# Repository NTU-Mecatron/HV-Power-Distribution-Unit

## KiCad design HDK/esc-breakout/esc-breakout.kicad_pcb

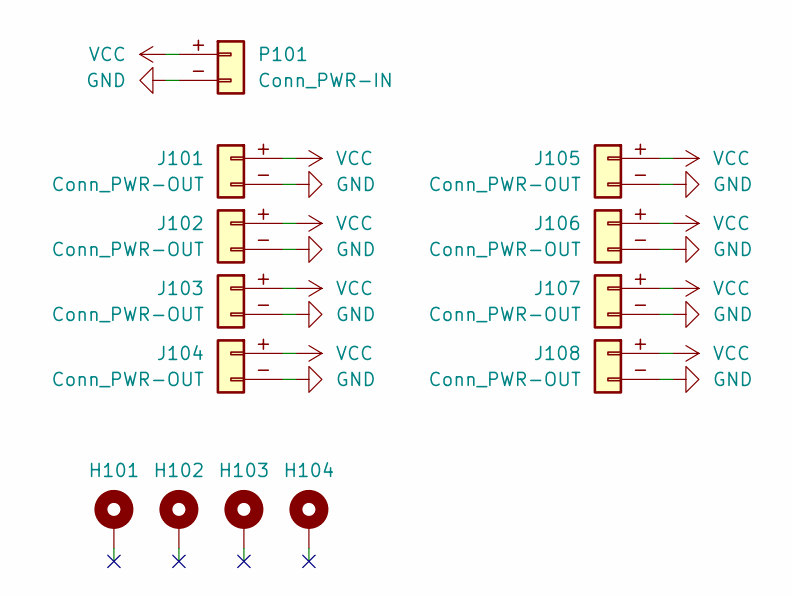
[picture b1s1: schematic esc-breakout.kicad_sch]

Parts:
H101, H102, H103, H104: MountingHole_Pad; MountingHole_3.2mm_M3_DIN965_Pad_TopBottom
J101, J102, J103, J104, J105, J106, J107, J108: Conn_PWR-OUT; AMASS_XT30UPB-F_1x02_P5.0mm_Vertical
P101: Conn_PWR-IN; AMASS_XT60-M_1x02_P7.20mm_Vertical

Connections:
GND: J101.- (Pin_2), J102.- (Pin_2), J103.- (Pin_2), J104.- (Pin_2), J105.- (Pin_2), J106.- (Pin_2), J107.- (Pin_2), J108.- (Pin_2), P101.- (Pin_2)
VCC: J101.+ (Pin_1), J102.+ (Pin_1), J103.+ (Pin_1), J104.+ (Pin_1), J105.+ (Pin_1), J106.+ (Pin_1), J107.+ (Pin_1), J108.+ (Pin_1), P101.+ (Pin_1)

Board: 2 copper layers, 13 parts (1 on the bottom side), 2 nets, no tracks yet.

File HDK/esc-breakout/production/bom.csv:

Designator,Footprint,Quantity,Value,LCSC Part #
"J101, J102, J103, J104, J105, J106, J107, J108",AMASS_XT30UPB-F_1x02_P5.0mm_Vertical,8,Conn_PWR-OUT,
P101,AMASS_XT60-M_1x02_P7.20mm_Vertical,1,Conn_PWR-IN,

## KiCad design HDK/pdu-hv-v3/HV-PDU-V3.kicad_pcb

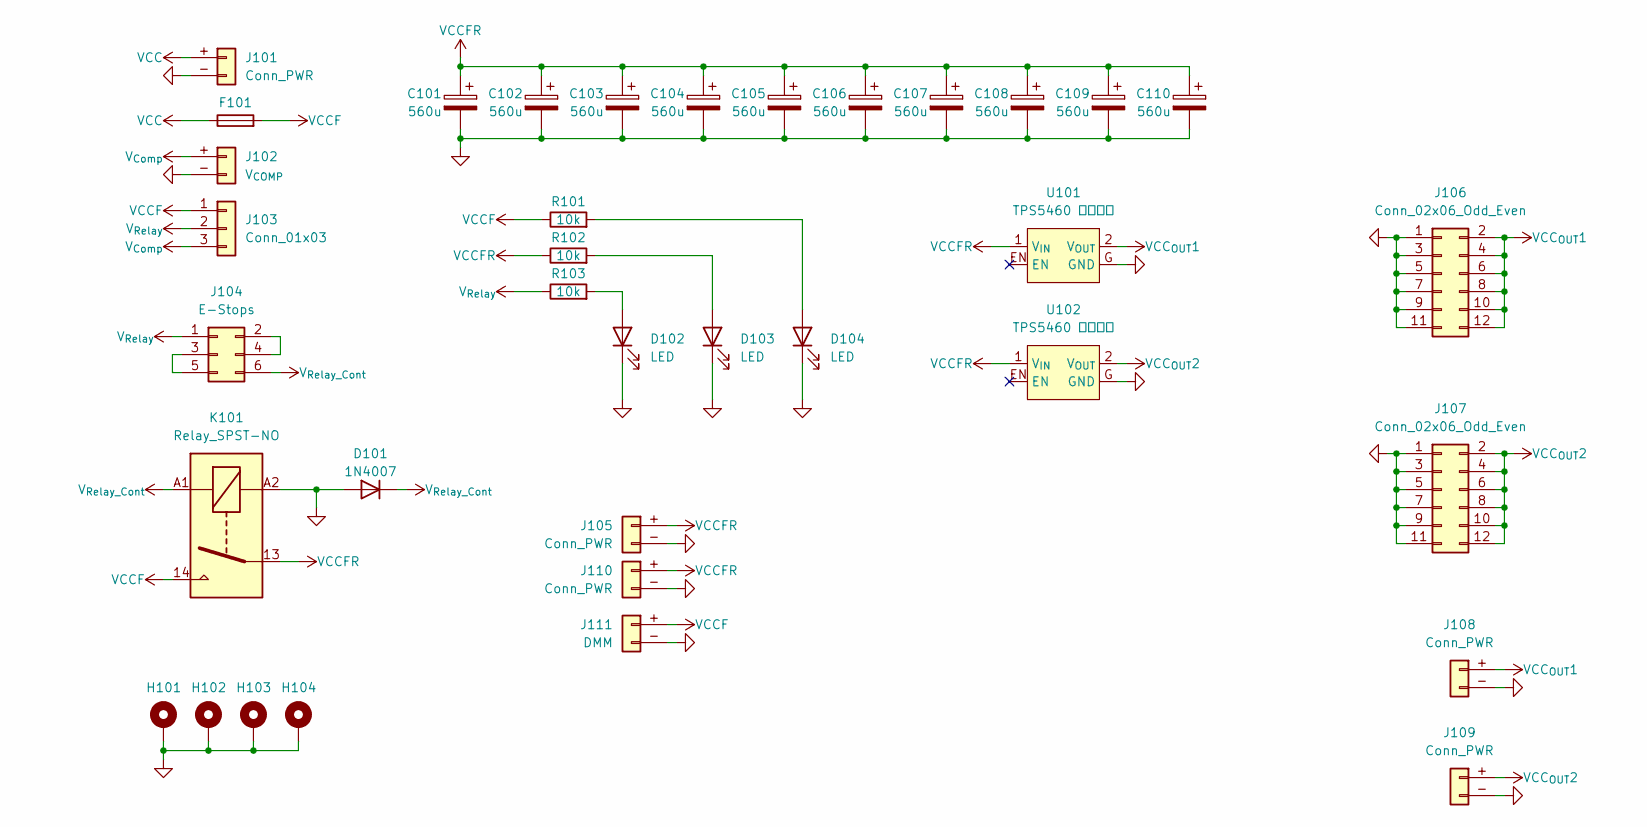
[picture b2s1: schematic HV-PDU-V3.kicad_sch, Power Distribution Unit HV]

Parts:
C101, C102, C103, C104, C105, C106, C107, C108, C109, C110: 560u; CP_Radial_D10.0mm_P5.00mm
D101: 1N4007; D_DO-35_SOD27_P7.62mm_Horizontal
D102, D103, D104: LED; LED_D5.0mm
F101: Fuse; FUSE-MCCQ-121
H101, H102, H103, H104: MountingHole_Pad_MP; MountingHole_3.2mm_M3_DIN965_Pad_TopBottom
J101: Conn_PWR; AMASS_XT60PW-M_1x02_P7.20mm_Horizontal
J102: V_{COMP}; JST_XH_B2B-XH-AM_1x02_P2.50mm_Vertical
J103: Conn_01x03; PinHeader_1x03_P2.54mm_Vertical
J104: E-Stops; PinHeader_2x03_P2.54mm_Vertical
J105: Conn_PWR; AMASS_XT60PW-F_1x02_P7.20mm_Horizontal
J106, J107: Conn_02x06_Odd_Even; PinHeader_2x06_P2.54mm_Vertical
J108, J109: Conn_PWR; AMASS_XT30UPB-F_1x02_P5.0mm_Vertical
J110: Conn_PWR; AMASS_XT60-M_1x02_P7.20mm_Vertical
J111: DMM; JST_XH_B2B-XH-AM_1x02_P2.50mm_Vertical
K101: Relay_SPST-NO; G8PM1AW7RDC12
R101, R102, R103: 10k; R_Axial_DIN0207_L6.3mm_D2.5mm_P7.62mm_Horizontal
U101, U102: TPS5460 康威科技

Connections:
GND: C101.2, C102.2, C103.2, C104.2, C105.2, C106.2, C107.2, C108.2, C109.2, C110.2, D101.2 (A), D102.1 (K), D103.1 (K), D104.1 (K), H101.1, H102.1, H103.1, H104.1, J101.- (Pin_2), J102.- (Pin_2), J105.- (Pin_2), J106.1, J106.3, J106.5, J106.7, J106.9, J106.11, J107.1, J107.3, J107.5, J107.7, J107.9, J107.11, J108.- (Pin_2), J109.- (Pin_2), J110.- (Pin_2), J111.- (Pin_2), K101.A2, U101.G (GND), U102.G (GND)
unnamed: D102.2 (A), R103.2
unnamed: D103.2 (A), R102.2
unnamed: D104.2 (A), R101.2
unnamed: J104.2, J104.4
unnamed: J104.3, J104.5
VCC: F101.1, J101.+ (Pin_1)
VCCF: F101.2, J103.1, J111.+ (Pin_1), K101.14, R101.1
VCCFR: C101.1, C102.1, C103.1, C104.1, C105.1, C106.1, C107.1, C108.1, C109.1, C110.1, J105.+ (Pin_1), J110.+ (Pin_1), K101.13, R102.1, U101.1 (V_{IN}), U102.1 (V_{IN})
VCC_{OUT}1: J106.2, J106.4, J106.6, J106.8, J106.10, J106.12, J108.+ (Pin_1), U101.2 (V_{OUT})
VCC_{OUT}2: J107.2, J107.4, J107.6, J107.8, J107.10, J107.12, J109.+ (Pin_1), U102.2 (V_{OUT})
V_{Comp}: J102.+ (Pin_1), J103.3
V_{Relay_Cont}: D101.1 (K), J104.6, K101.A1
V_{Relay}: J103.2, J104.1, R103.1

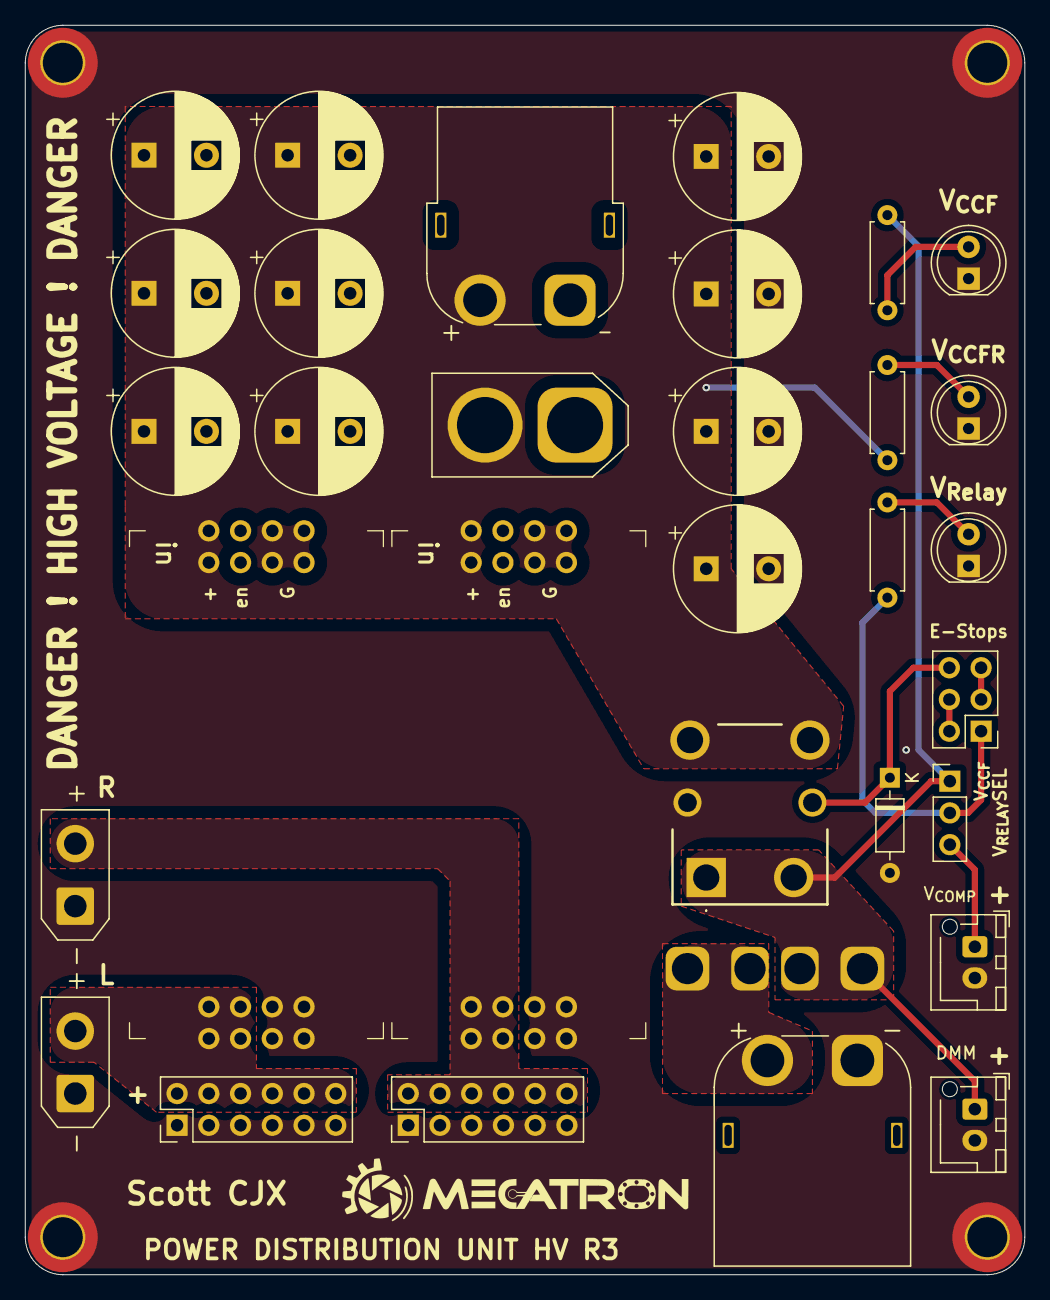
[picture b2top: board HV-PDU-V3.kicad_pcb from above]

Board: 2 copper layers, 80.0 x 100.0 mm, 36 parts (0 on the bottom side), 14 nets.

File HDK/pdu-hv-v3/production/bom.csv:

Designator,Footprint,Quantity,Value,LCSC Part #
"C101, C102, C103, C104, C105, C106, C107, C108, C109, C110",CP_Radial_D10.0mm_P5.00mm,10,560u,
D101,D_DO-35_SOD27_P7.62mm_Horizontal,1,1N4007,
"D102, D103, D104",LED_D5.0mm,3,LED,
F101,FUSE-MCCQ-121,1,Fuse,
J101,AMASS_XT60PW-M_1x02_P7.20mm_Horizontal,1,Conn_PWR,
J102,JST_XH_B2B-XH-AM_1x02_P2.50mm_Vertical,1,V_{COMP},
J103,PinHeader_1x03_P2.54mm_Vertical,1,Conn_01x03,
J104,PinHeader_2x03_P2.54mm_Vertical,1,E-Stops,
J105,AMASS_XT60PW-F_1x02_P7.20mm_Horizontal,1,Conn_PWR,
"J106, J107",PinHeader_2x06_P2.54mm_Vertical,2,Conn_02x06_Odd_Even,
"J108, J109",AMASS_XT30UPB-F_1x02_P5.0mm_Vertical,2,Conn_PWR,
J110,AMASS_XT60-M_1x02_P7.20mm_Vertical,1,Conn_PWR,
J111,JST_XH_B2B-XH-AM_1x02_P2.50mm_Vertical,1,DMM,
K101,G8PM1AW7RDC12,1,Relay_SPST-NO,
"R101, R102, R103",R_Axial_DIN0207_L6.3mm_D2.5mm_P7.62mm_Horizontal,3,10k,
"U101, U102",TPS5460 康威科技,2,TPS5460 康威科技,

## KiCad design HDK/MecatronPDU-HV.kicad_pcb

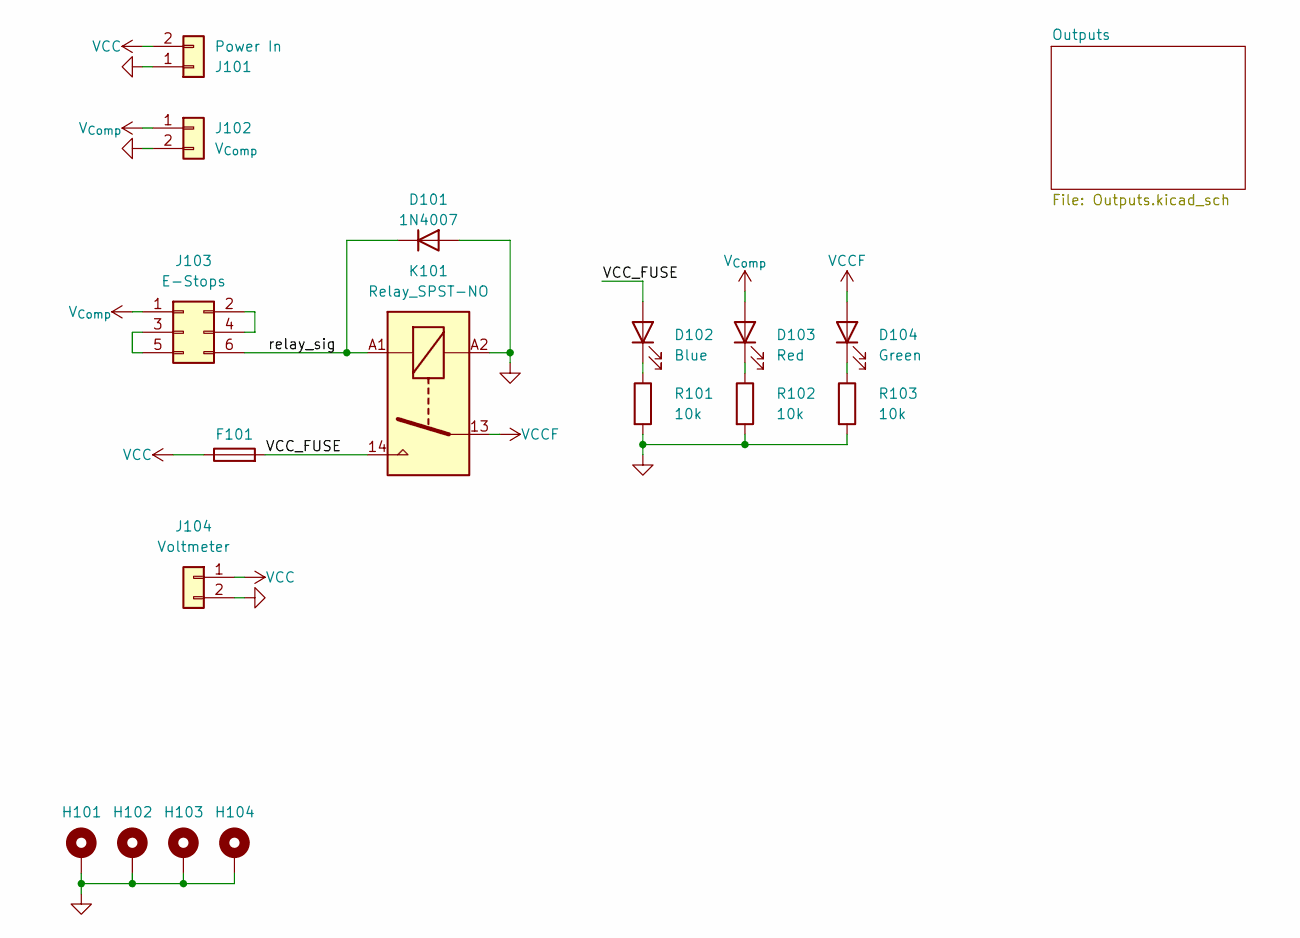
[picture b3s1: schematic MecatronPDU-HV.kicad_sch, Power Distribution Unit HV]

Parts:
D101: 1N4007; D_DO-35_SOD27_P7.62mm_Horizontal
D102: Blue; LED_D5.0mm_Clear
D103: Red; LED_D5.0mm_Clear
D104: Green; LED_D5.0mm_Clear
F101: Fuse; FUSE-MCCQ-121
H101, H102, H103, H104: MountingHole_Pad_MP; MountingHole_5.3mm_M5_ISO7380_Pad_TopBottom
J101: Power In; AMASS_XT60PW-M_1x02_P7.20mm_Horizontal
J102: V_{Comp}; JST_XH_B2B-XH-AM_1x02_P2.50mm_Vertical
J103: E-Stops; PinHeader_2x03_P2.54mm_Vertical
J104: Voltmeter; JST_XH_B2B-XH-AM_1x02_P2.50mm_Vertical
K101: Relay_SPST-NO; G8PM1AW7RDC12
R101, R102, R103: 10k; R_Axial_DIN0204_L3.6mm_D1.6mm_P5.08mm_Horizontal

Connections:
/VCC_FUSE: D102.2 (A), F101.2, K101.14
/relay_sig: D101.1 (K), J103.6, K101.A1
GND: D101.2 (A), H101.1, H102.1, H103.1, H104.1, J101.1, J102.2, J104.2, K101.A2, R101.2, R102.2, R103.2; also elsewhere on the board
unnamed: D102.1 (K), R101.1
unnamed: D103.1 (K), R102.1
unnamed: D104.1 (K), R103.1
unnamed: J103.2, J103.4
unnamed: J103.3, J103.5
VCC: F101.1, J101.2, J104.1
VCCF: D104.2 (A), K101.13; also elsewhere on the board
V_{Comp}: D103.2 (A), J102.1, J103.1

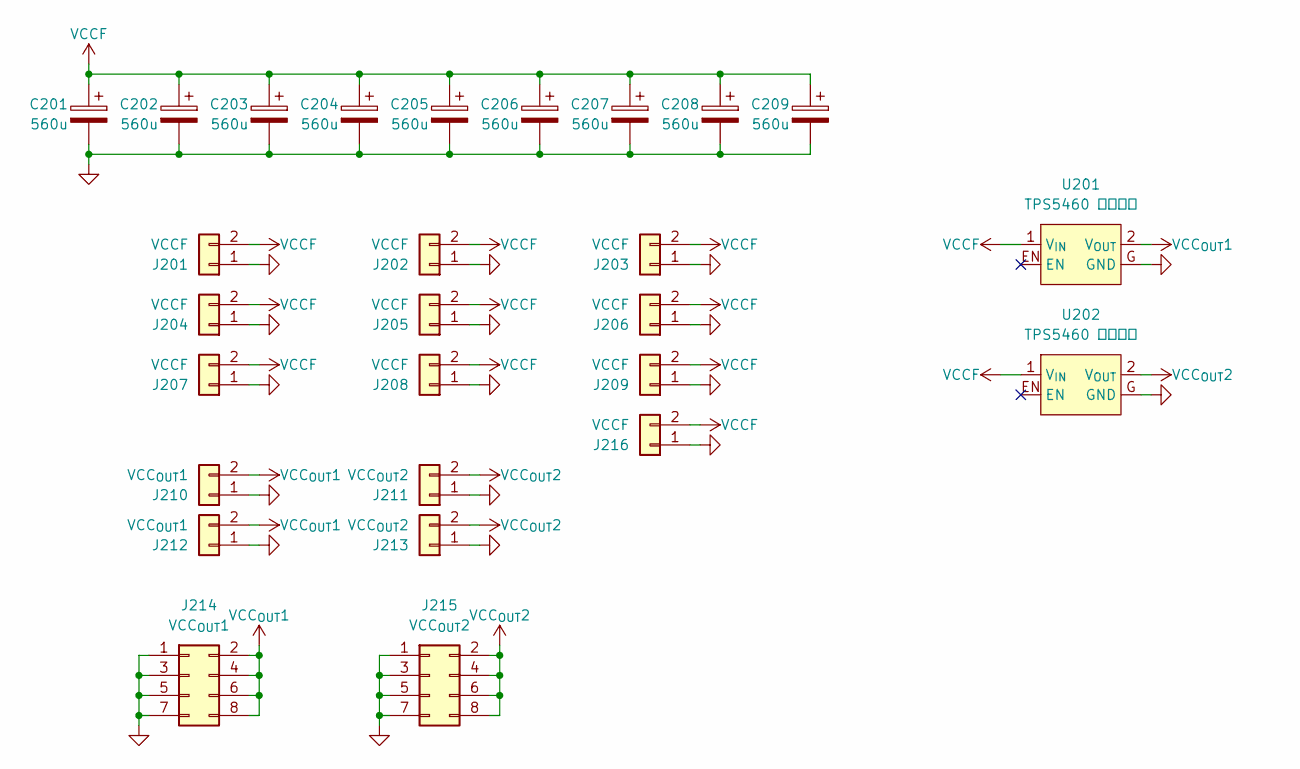
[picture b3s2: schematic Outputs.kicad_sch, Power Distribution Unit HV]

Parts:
C201, C202, C203, C204, C205, C206, C207, C208, C209: 560u; CP_Radial_D10.0mm_P5.00mm
J201, J202, J203, J204, J205, J206: VCCF; AMASS_XT30PW-F_1x02_P2.50mm_Horizontal
J207, J208, J209, J216: VCCF; AMASS_XT30U-F_1x02_P5.0mm_Vertical
J210, J212: VCC_{OUT}1; AMASS_XT30PW-F_1x02_P2.50mm_Horizontal
J211, J213: VCC_{OUT}2; AMASS_XT30PW-F_1x02_P2.50mm_Horizontal
J214: VCC_{OUT}1; PinHeader_2x04_P2.54mm_Vertical
J215: VCC_{OUT}2; PinHeader_2x04_P2.54mm_Vertical
U201, U202: TPS5460 康威科技

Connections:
GND: C201.2, C202.2, C203.2, C204.2, C205.2, C206.2, C207.2, C208.2, C209.2, J201.1, J202.1, J203.1, J204.1, J205.1, J206.1, J207.1, J208.1, J209.1, J210.1, J211.1, J212.1, J213.1, J214.1, J214.3, J214.5, J214.7, J215.1, J215.3, J215.5, J215.7, J216.1, U201.G (GND), U202.G (GND); also elsewhere on the board
VCCF: C201.1, C202.1, C203.1, C204.1, C205.1, C206.1, C207.1, C208.1, C209.1, J201.2, J202.2, J203.2, J204.2, J205.2, J206.2, J207.2, J208.2, J209.2, J216.2, U201.1 (V_{IN}), U202.1 (V_{IN}); also elsewhere on the board
VCC_{OUT}1: J210.2, J212.2, J214.2, J214.4, J214.6, J214.8, U201.2 (V_{OUT})
VCC_{OUT}2: J211.2, J213.2, J215.2, J215.4, J215.6, J215.8, U202.2 (V_{OUT})

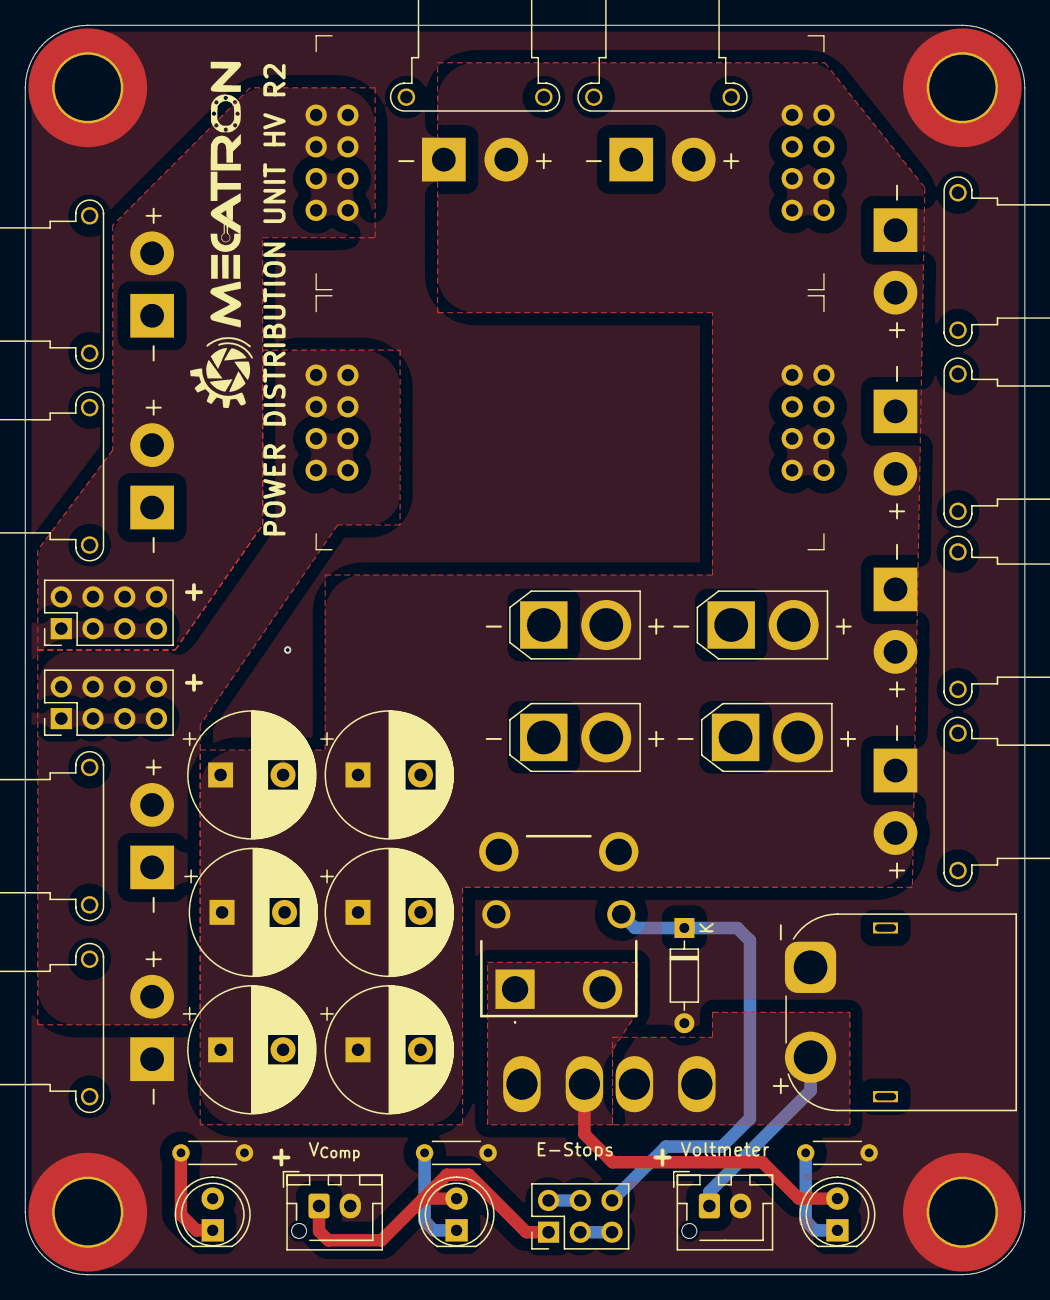
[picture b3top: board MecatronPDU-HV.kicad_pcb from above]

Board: 2 copper layers, 80.0 x 100.0 mm, 41 parts (0 on the bottom side), 13 nets.

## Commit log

2024-09-18 added R1
2024-09-18 Deployed e2aa1f4 with MkDocs version: 1.6.1
2024-10-16 init v2
2024-10-17 updated rev2
2024-11-14 tentative rev3
2024-12-02 rev3
2025-05-02 Update HV-PDU-V3.step
    2/5 step file
2025-05-02 update with step from wm

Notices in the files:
HDK/MecatronPDU-HV.kicad_pcb:
License :CERN-OHL-S-2.0
Copyright © Mecatron
